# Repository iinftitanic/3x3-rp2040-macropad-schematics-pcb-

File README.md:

basic specs drop :

-> 9 mechanical keys (3×3 layout)

-> RP2040 microcontroller (XIAO RP2040)

-> Diode matrix to prevent ghosting

-> Designed in KiCad

-> Compatible with keyboard firmware such as KMK or QMK

its a simple micropad proj inspired by the steam deck (too broke to get one)
its got 2 modes, ones a media mode n the others a game mode... istg KiCad's so annoying it didnt have the xiao-rp2040 microcontroller.. i had to customise the number of GPIO PINS on it so that it coordinates with the rows n colums ! 

yea so looks WAYY MORE useable now

then i just joined the wires, assembled the diodes (idk why but i put 9 in there for some reason lmao... removed em later), connected the switches to the diodes (def aint usin a 10k resistor)

this is the final product (of the schematic ofc) and now i just generated the PCB and it looks someewhat like thiss ! (might tweak sm lateron)

yep so thats it pretty much it for the hardware part
ive now coded it up too ! took some help from chatgpt nd claude but yeah its up and boomingg ! ive got the oled screen to work too... it can display basic things like volume, the mode im using my mocrocontroller on and etc...

yep now the designs for the case are made too (i wont say ready as they are still needing some revision)

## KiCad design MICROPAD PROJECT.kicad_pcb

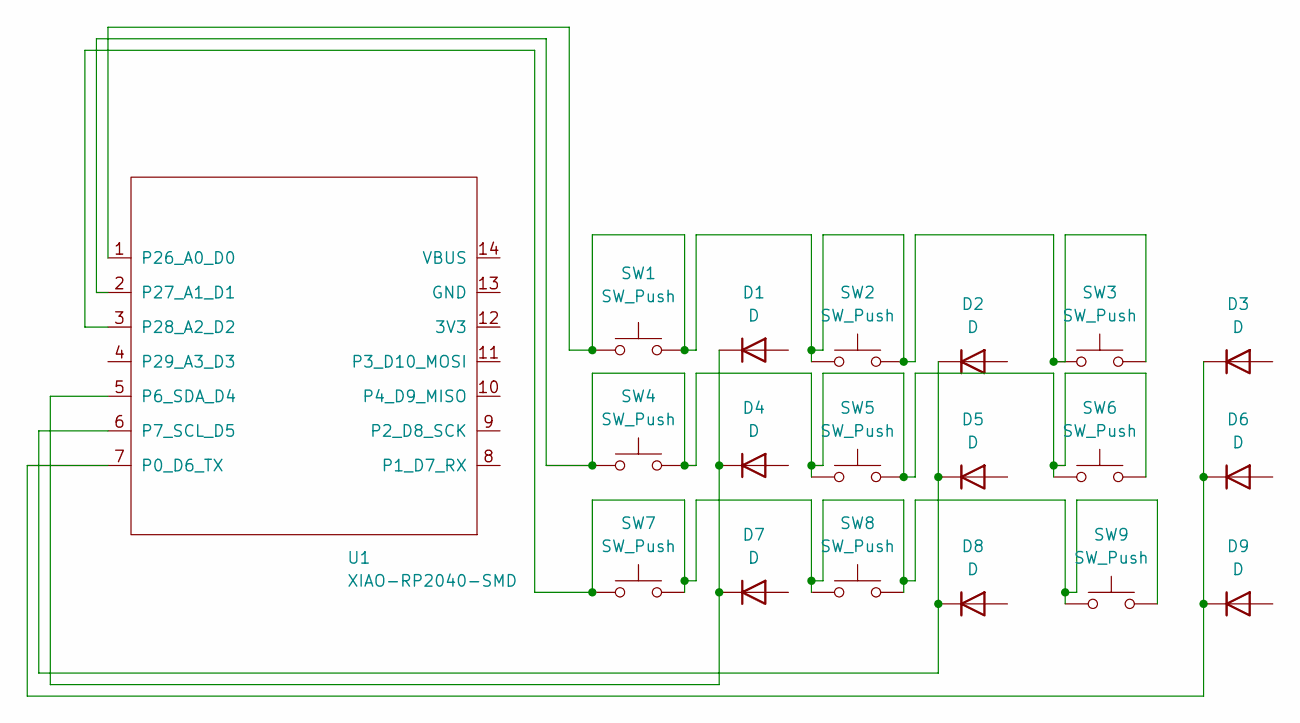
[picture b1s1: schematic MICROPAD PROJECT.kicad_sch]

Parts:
D1, D2, D3, D4, D5, D6, D7, D8, D9: D; D_SOD-123
SW1, SW2, SW3, SW4, SW5, SW6, SW7, SW8, SW9: SW_Push; SW_SPST_EVQP7A
U1: XIAO-RP2040-SMD

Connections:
unnamed: D1.1 (K), D4.1 (K), D7.1 (K), U1.5 (P6_SDA_D4)
unnamed: D2.1 (K), D5.1 (K), D8.1 (K), U1.6 (P7_SCL_D5)
unnamed: D3.1 (K), D6.1 (K), D9.1 (K), U1.7 (P0_D6_TX)
unnamed: SW1.1, SW1.2, SW2.1, SW2.2, SW3.1, SW3.2, U1.1 (P26_A0_D0)
unnamed: SW4.1, SW4.2, SW5.1, SW5.2, SW6.1, SW6.2, U1.2 (P27_A1_D1)
unnamed: SW7.1, SW7.2, SW8.1, SW8.2, SW9.1, SW9.2, U1.3 (P28_A2_D2)

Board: 2 copper layers, 19 parts (0 on the bottom side), 6 nets, no tracks yet.

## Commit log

2026-03-08 commit 1 -> README.md
2026-03-31 README.md
